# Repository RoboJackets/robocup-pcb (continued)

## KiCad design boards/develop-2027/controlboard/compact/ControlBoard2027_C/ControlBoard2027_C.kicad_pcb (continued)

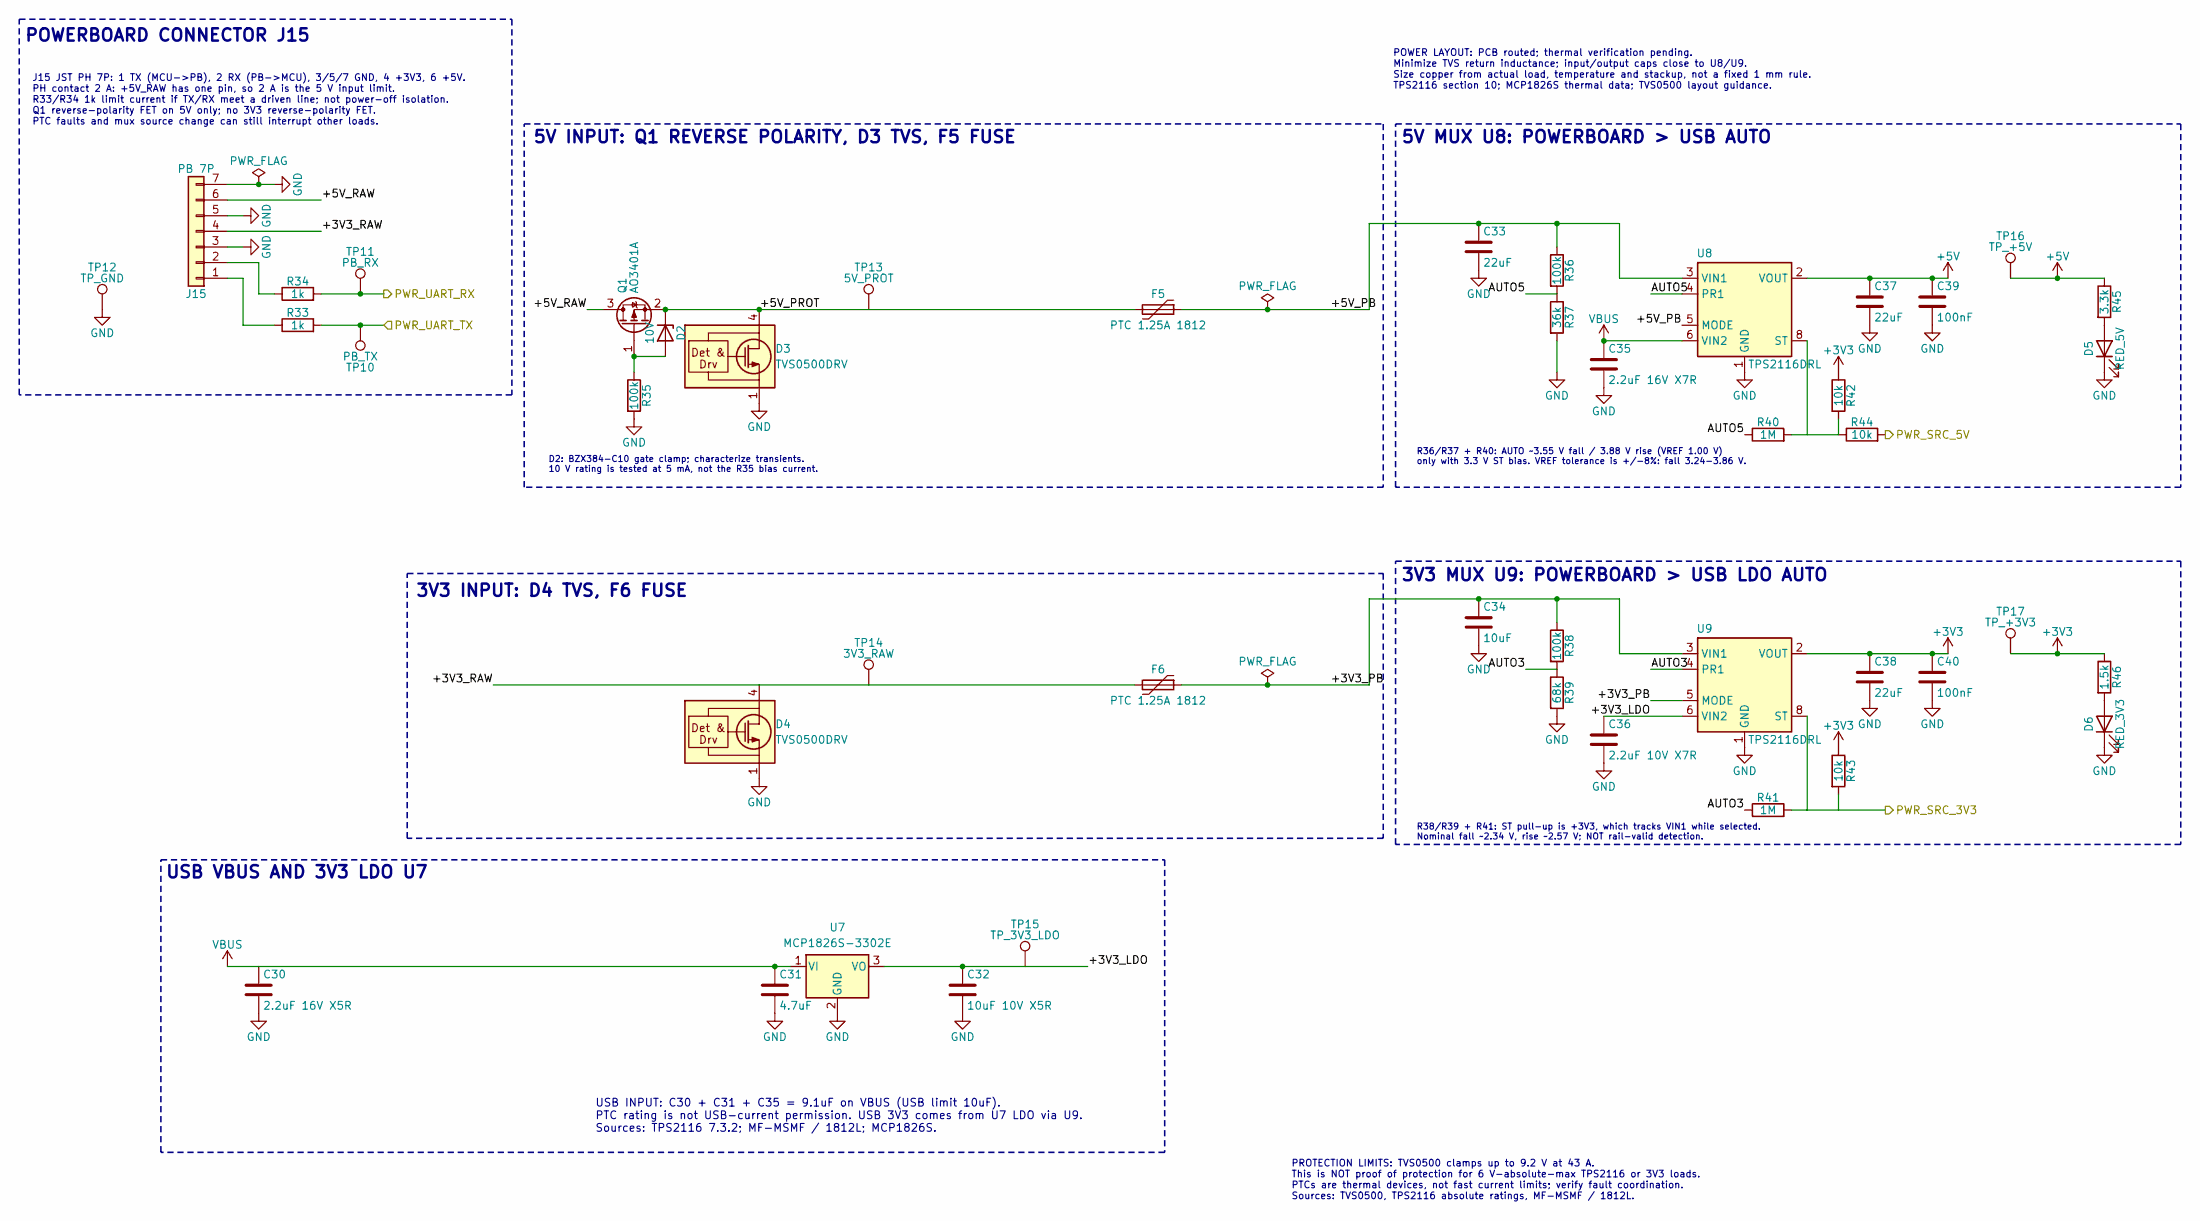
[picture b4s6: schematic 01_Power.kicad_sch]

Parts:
C30: 2.2uF 16V X5R; C_0603_1608Metric; Rating 16V X5R; MPN Samsung CL10A225KO8NNNC; LCSC C23630
C31: 4.7uF; C_0603_1608Metric; Rating 16V X5R; MPN TDK C1608X5R1C475K080AC; LCSC C19666
C32: 10uF 10V X5R; C_0603_1608Metric; Rating 10V X5R 10%; MPN Taiyo Yuden LMK107BBJ106MALT; LCSC C19702
C33, C37: 22uF; C_0805_2012Metric; Rating 25V X5R 20%; MPN Samsung CL21A226MOQNNNE; LCSC C45783
C34: 10uF; C_0603_1608Metric; Rating 10V X5R 10%; MPN Taiyo Yuden LMK107BBJ106MALT; LCSC C19702
C35: 2.2uF 16V X7R; C_0805_2012Metric; Rating 16V X7R; MPN Samsung CL21B225KOFNNNE; LCSC C28234
C36: 2.2uF 10V X7R; C_0603_1608Metric; Rating 10V X7R; MPN Samsung CL10B225KP8NNNC; LCSC C100082
C38: 22uF; C_0603_1608Metric; Rating 6.3V X5R 20%; MPN Taiyo Yuden JMK107BBJ226MA-T; LCSC C59461
C39, C40: 100nF; C_0402_1005Metric; Rating 16V X7R; MPN Samsung CL05B104KO5NNNC; LCSC C1525
D2: 10V; D_SOD-323; MPN Nexperia BZX384-C10,115; LCSC C96228
D3, D4: TVS0500DRV; WSON-6-1EP_2x2mm_P0.65mm_EP1x1.6mm; MPN TI TVS0500DRVR; LCSC C609571
D5: RED_5V; LED_0603_1608Metric; MPN Kingbright APT1608EC; LCSC C5554143
D6: RED_3V3; LED_0603_1608Metric; MPN Kingbright APT1608EC; LCSC C5554143
F5, F6: PTC 1.25A 1812; Fuse_Bourns_MF-MSMF_1812; MPN Bourns MF-MSMF125/16X-2; LCSC C207067
J15: PB 7P; JST_PH_S7B-PH-K_1x07_P2.00mm_Horizontal; MPN JST S7B-PH-K-S(LF)(SN); LCSC C157917
Q1: AO3401A; SOT-23; MPN AOS AO3401A; LCSC C15127
R33, R34: 1k; R_0402_1005Metric; Rating 1%; MPN Yageo RC0402FR-071KL; LCSC C11702
R35, R36, R38: 100k; R_0603_1608Metric; Rating 1%; MPN Yageo RC0603FR-07100KL; LCSC C25803
R37: 36k; R_0603_1608Metric; Rating 1%; MPN Yageo RC0603FR-0736KL; LCSC C114619
R39: 68k; R_0603_1608Metric; Rating 1%; MPN Yageo RC0603FR-0768KL; LCSC C23231
R40, R41: 1M; R_0603_1608Metric; Rating 1%; MPN Yageo RC0603FR-071ML; LCSC C22935
R42, R43, R44: 10k; R_0603_1608Metric; Rating 1%; MPN Panasonic ERJ-3EKF1002V; LCSC C25804
R45: 3.3k; R_0603_1608Metric; Rating 1%; MPN Yageo RC0603FR-073K3L; LCSC C22978
R46: 1.5k; R_0603_1608Metric; Rating 1%; MPN Yageo RC0603FR-071K5L; LCSC C22843
TP10: PB_TX; TestPoint_Pad_1.5x1.5mm
TP11: PB_RX; TestPoint_Pad_1.5x1.5mm
TP12: TP_GND; TestPoint_Pad_1.5x1.5mm
TP13: 5V_PROT; TestPoint_Pad_1.5x1.5mm
TP14: 3V3_RAW; TestPoint_Pad_1.5x1.5mm
TP15: TP_3V3_LDO; TestPoint_Pad_1.5x1.5mm
TP16: TP_+5V; TestPoint_Pad_1.5x1.5mm
TP17: TP_+3V3; TestPoint_Pad_1.5x1.5mm
U7: MCP1826S-3302E; SOT-223-3_TabPin2; Rating 1A, VIN 6.0V max, 3.3V +-2.5%; MPN Microchip MCP1826S-3302E/DB; LCSC C638624
U8, U9: TPS2116DRL; TI_TPS2116_DRL0008A; MPN TI TPS2116DRLR; LCSC C3235557

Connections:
+3V3: C38.1, C40.1, R42.1, R43.1, R46.1, TP17.1 (1_1), U9.2 (VOUT), U9.7 (VOUT); also elsewhere on the board
+5V: C37.1, C39.1, R45.1, TP16.1 (1_1), U8.2 (VOUT), U8.7 (VOUT); also elsewhere on the board
/MCU/PWR_SRC_3V3: R41.2, R43.2, U9.8 (ST); also elsewhere on the board
/MCU/PWR_SRC_5V: R44.2; also elsewhere on the board
/MCU/PWR_UART_RX: R34.2, TP11.1 (1_1); also elsewhere on the board
/MCU/PWR_UART_TX: R33.2, TP10.1 (1_1); also elsewhere on the board
/Power/+3V3_LDO: C32.1, C36.1, TP15.1 (1_1), U7.3 (VO), U9.6 (VIN2)
/Power/+3V3_RAW: D4.4 (IN), D4.5 (IN), D4.6 (IN), F6.2, J15.4, TP14.1 (1_1)
/Power/+5V_PROT: D2.1 (K), D3.4 (IN), D3.5 (IN), D3.6 (IN), F5.2, Q1.2 (S), TP13.1 (1_1)
/Power/+5V_RAW: J15.6, Q1.3 (D)
/Power/AUTO3: R38.2, R39.1, R41.1, U9.4 (PR1)
/Power/AUTO5: R36.2, R37.1, R40.1, U8.4 (PR1)
unnamed: D2.2 (A), Q1.1 (G), R35.1
unnamed: D5.2 (A), R45.2
unnamed: D6.2 (A), R46.2
unnamed: J15.1, R33.1
unnamed: J15.2, R34.1
unnamed: R40.2, R42.2, R44.1, U8.8 (ST)
VBUS: C30.1, C31.1, C35.1, U7.1 (VI), U8.6 (VIN2); also elsewhere on the board

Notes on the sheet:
POWER LAYOUT: PCB routed; thermal verification pending. Minimize TVS return inductance; input/output caps close to U8/U9. Size copper from actual load, temperature and stackup, not a fixed 1 mm rule. TPS2116 section 10; MCP1826S thermal data; TVS0500 layout guidance.
3V3 MUX U9: POWERBOARD > USB LDO AUTO
USB INPUT: C30 + C31 + C35 = 9.1uF on VBUS (USB limit 10uF). PTC rating is not USB-current permission. USB 3V3 comes from U7 LDO via U9. Sources: TPS2116 7.3.2; MF-MSMF / 1812L; MCP1826S.
R36/R37 + R40: AUTO ~3.55 V fall / 3.88 V rise (VREF 1.00 V) only with 3.3 V ST bias. VREF tolerance is +/-8%: fall 3.24-3.86 V.
D2: BZX384-C10 gate clamp; characterize transients. 10 V rating is tested at 5 mA, not the R35 bias current.
J15 JST PH 7P: 1 TX (MCU->PB), 2 RX (PB->MCU), 3/5/7 GND, 4 +3V3, 6 +5V. PH contact 2 A: +5V_RAW has one pin, so 2 A is the 5 V input limit. R33/R34 1k limit current if TX/RX meet a driven line; not power-off isolation. Q1 reverse-polarity FET on 5V only; no 3V3 reverse-polarity FET. PTC faults and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
5V INPUT: Q1 REVERSE POLARITY, D3 TVS, F5 FUSE
5V MUX U8: POWERBOARD > USB AUTO
PROTECTION LIMITS: TVS0500 clamps up to 9.2 V at 43 A. This is NOT proof of protection for 6 V-absolute-max TPS2116 or 3V3 loads. PTCs are thermal devices, not fast current limits; verify fault coordination. Sources: TVS0500, TPS2116 absolute ratings, MF-MSMF / 1812L.
3V3 INPUT: D4 TVS, F6 FUSE
USB VBUS AND 3V3 LDO U7
POWERBOARD CONNECTOR J15
R38/R39 + R41: ST pull-up is +3V3, which tracks VIN1 while selected. Nominal fall ~2.34 V, rise ~2.57 V; NOT rail-valid detection.

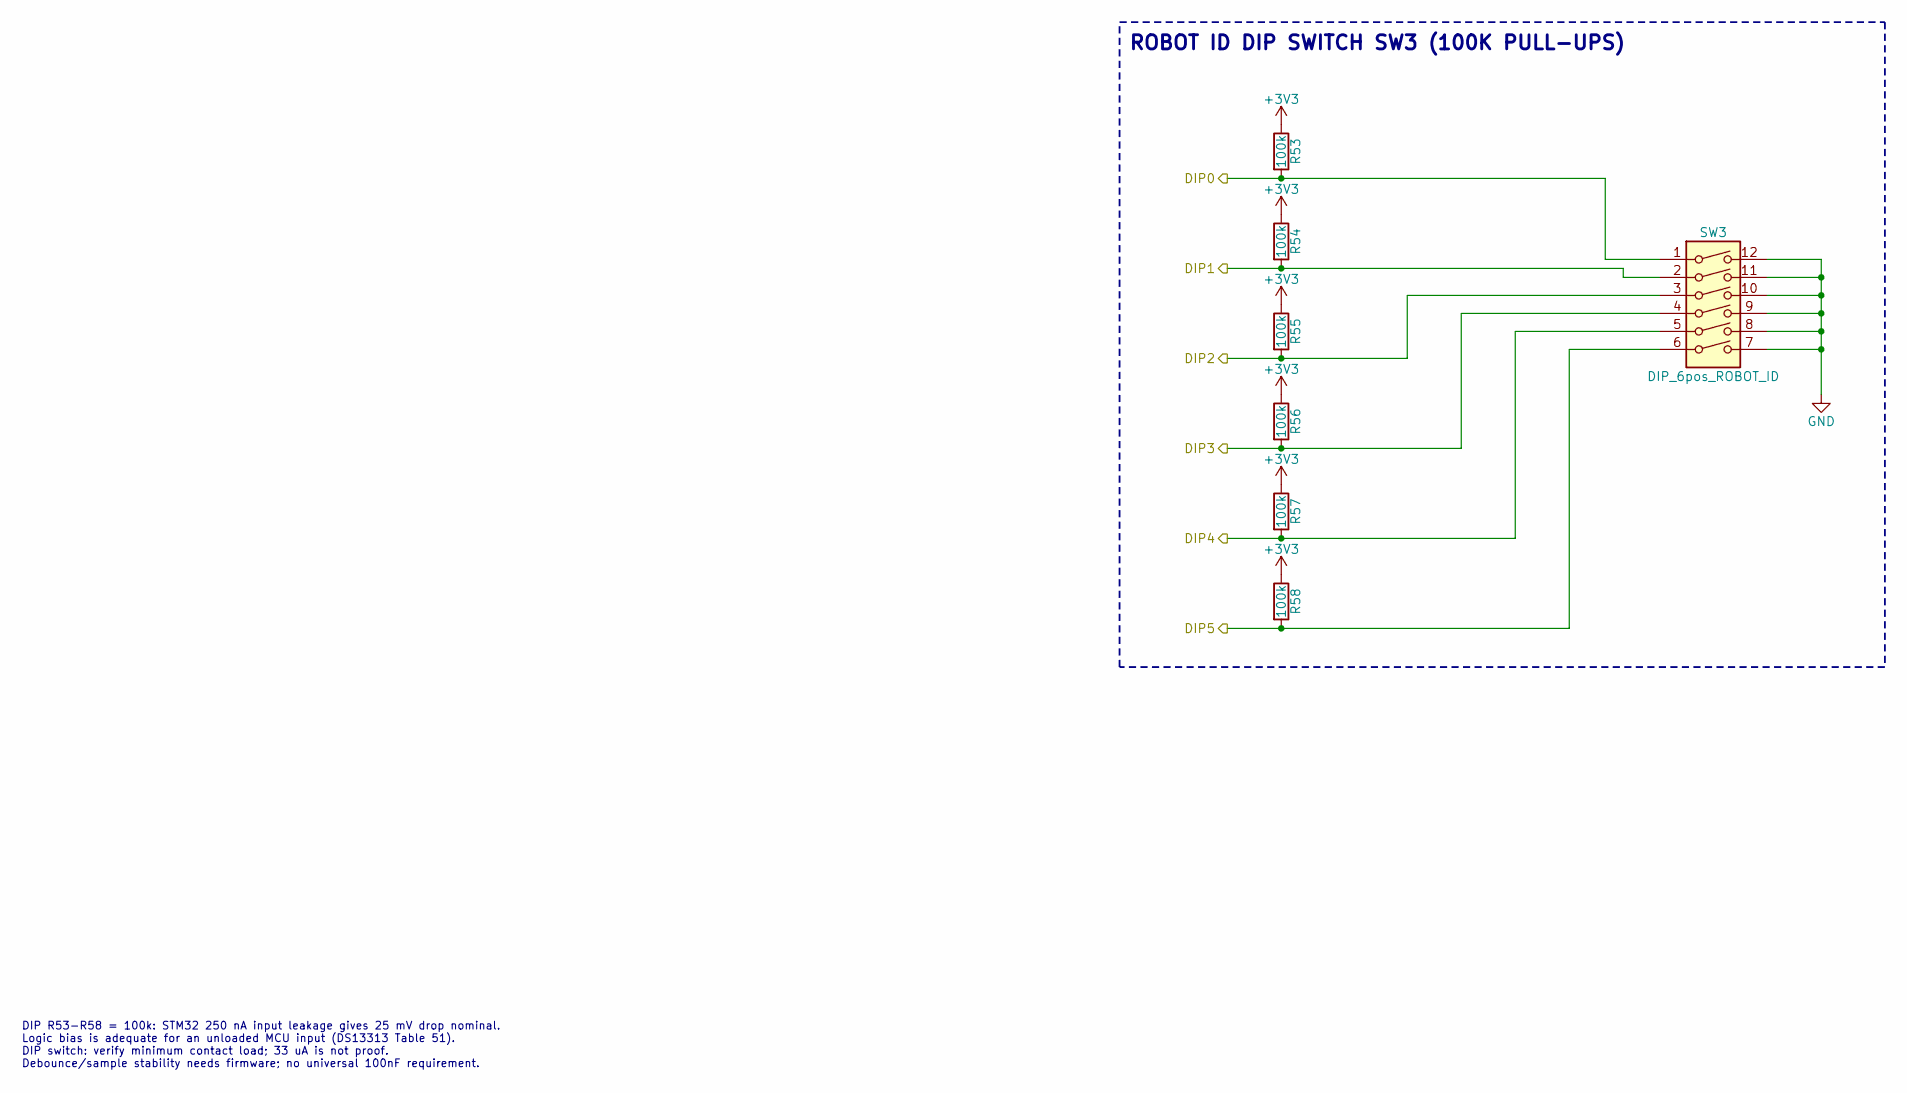
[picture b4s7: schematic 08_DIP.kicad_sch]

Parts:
R53, R54, R55, R56, R57, R58: 100k; R_0603_1608Metric; Rating 1%; MPN Yageo RC0603FR-07100KL; LCSC C25803
SW3: DIP_6pos_ROBOT_ID; SW_DIP_SPSTx06_Slide_6.7x16.8mm_W7.62mm_P2.54mm_LowProfile; MPN CTS 209-6MS; LCSC C129072

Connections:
+3V3: R53.1, R54.1, R55.1, R56.1, R57.1, R58.1; also elsewhere on the board
/MCU/DIP0: R53.2, SW3.1; also elsewhere on the board
/MCU/DIP1: R54.2, SW3.2; also elsewhere on the board
/MCU/DIP2: R55.2, SW3.3; also elsewhere on the board
/MCU/DIP3: R56.2, SW3.4; also elsewhere on the board
/MCU/DIP4: R57.2, SW3.5; also elsewhere on the board
/MCU/DIP5: R58.2, SW3.6; also elsewhere on the board

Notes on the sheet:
DIP R53-R58 = 100k: STM32 250 nA input leakage gives 25 mV drop nominal. Logic bias is adequate for an unloaded MCU input (DS13313 Table 51). DIP switch: verify minimum contact load; 33 uA is not proof. Debounce/sample stability needs firmware; no universal 100nF requirement.
ROBOT ID DIP SWITCH SW3 (100K PULL-UPS)

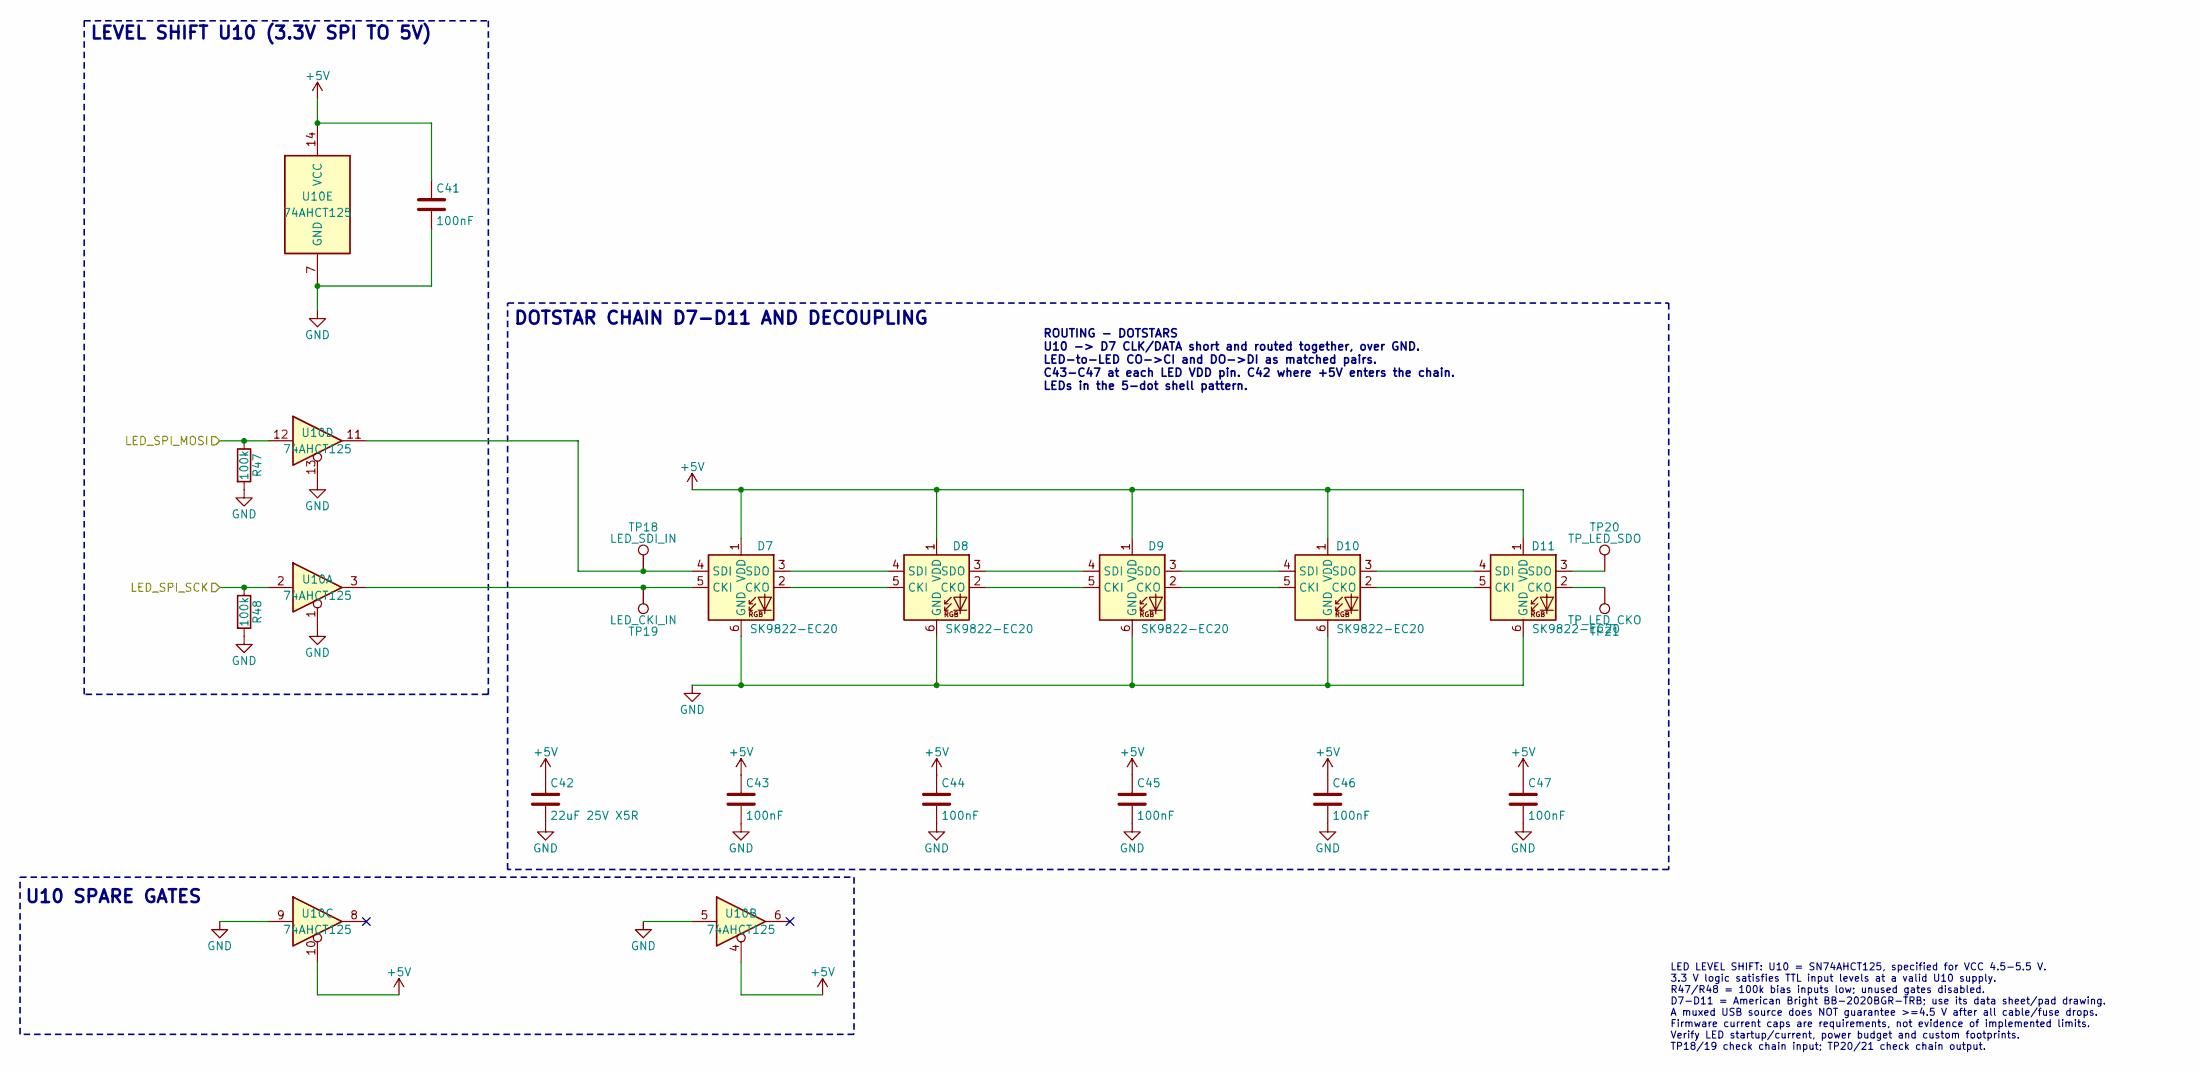
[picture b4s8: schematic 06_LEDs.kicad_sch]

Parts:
C41, C43, C44, C45, C46, C47: 100nF; C_0402_1005Metric; Rating 16V X7R; MPN Samsung CL05B104KO5NNNC; LCSC C1525
C42: 22uF 25V X5R; C_0805_2012Metric; Rating 25V X5R 20%; MPN Samsung CL21A226MOQNNNE; LCSC C45783
D7, D8, D9, D10, D11: SK9822-EC20; OPSCO_SK9822-EC20; MPN OPSCO SK9822-EC20; LCSC C2909059
R47, R48: 100k; R_0402_1005Metric; Rating 1%; MPN Yageo RC0402FR-07100KL; LCSC C25741
TP18: LED_SDI_IN; TestPoint_Pad_1.5x1.5mm
TP19: LED_CKI_IN; TestPoint_Pad_1.5x1.5mm
TP20: TP_LED_SDO; TestPoint_Pad_1.5x1.5mm
TP21: TP_LED_CKO; TestPoint_Pad_1.5x1.5mm
U10: 74AHCT125; SO-14_3.9x8.65mm_P1.27mm; MPN TI SN74AHCT125DR; LCSC C155176

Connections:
+5V: C41.1, C42.1, C43.1, C44.1, C45.1, C46.1, C47.1, D7.1 (VDD), D8.1 (VDD), D9.1 (VDD), D10.1 (VDD), D11.1 (VDD), U10.4, U10.10, U10.14 (VCC); also elsewhere on the board
/DotStar LEDs/LED_SPI_MOSI: R47.1, U10.12; also elsewhere on the board
/DotStar LEDs/LED_SPI_SCK: R48.1, U10.2; also elsewhere on the board
unnamed: D7.5 (CKI), TP19.1 (1_1), U10.3
unnamed: D7.2 (CKO), D8.5 (CKI)
unnamed: D7.4 (SDI), TP18.1 (1_1), U10.11
unnamed: D7.3 (SDO), D8.4 (SDI)
unnamed: D8.2 (CKO), D9.5 (CKI)
unnamed: D8.3 (SDO), D9.4 (SDI)
unnamed: D9.2 (CKO), D10.5 (CKI)
unnamed: D10.2 (CKO), D11.5 (CKI)
unnamed: D9.3 (SDO), D10.4 (SDI)
unnamed: D10.3 (SDO), D11.4 (SDI)
unnamed: D11.2 (CKO), TP21.1 (1_1)
unnamed: D11.3 (SDO), TP20.1 (1_1)

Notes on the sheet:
LED LEVEL SHIFT: U10 = SN74AHCT125, specified for VCC 4.5-5.5 V. 3.3 V logic satisfies TTL input levels at a valid U10 supply. R47/R48 = 100k bias inputs low; unused gates disabled. D7-D11 = American Bright BB-2020BGR-TRB; use its data sheet/pad drawing. A muxed USB source does NOT guarantee >=4.5 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
LEVEL SHIFT U10 (3.3V SPI TO 5V)
U10 SPARE GATES
DOTSTAR CHAIN D7-D11 AND DECOUPLING
ROUTING - DOTSTARS U10 -> D7 CLK/DATA short and routed together, over GND. LED-to-LED CO->CI and DO->DI as matched pairs. C43-C47 at each LED VDD pin. C42 where +5V enters the chain. LEDs in the 5-dot shell pattern.

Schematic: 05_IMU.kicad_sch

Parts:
C48, C49: 100nF; C_0402_1005Metric; Rating 16V X7R; MPN Samsung CL05B104KO5NNNC; LCSC C1525
U11: LSM6DSV320X; ST_LGA-14L_2.5x3mm_P0.5mm; MPN ST LSM6DSV320XTR

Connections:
+3V3: C48.1, C49.1, U11.5 (VDDIO), U11.8 (VDD), U11.12 (CS); also elsewhere on the board
/IMU/ACCEL_EXTI: U11.4 (INT1); also elsewhere on the board
/IMU/GYRO_EXTI: U11.9 (INT2); also elsewhere on the board
/IMU/IMU_I2C_SCL: U11.13 (SCL); also elsewhere on the board
/IMU/IMU_I2C_SDA: U11.14 (SDA); also elsewhere on the board

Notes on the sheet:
ROUTING - IMU C48 (VDDIO pin 5), C49 (VDD pin 8): 100nF, as close to the pins as possible. CS to VDDIO = I2C. TA0, SDx, SCx to GND: address 0x6A, mode 1 (DS14623 Fig. 27). OCS_aux/SDO_aux open. No traces or vias under the package.
IMU U11 LSM6DSV320X: I2C (0x6A), INT1/INT2 INTERRUPTS
INTERRUPTS: INT1 -> ACCEL_EXTI (PF3), INT2 -> GYRO_EXTI (PF2). Both are push-pull and are driven low from power-up (DS14623 Table 25), so no pull-downs are fitted. Route data-ready or events to them with INT1_CTRL/INT2_CTRL.

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
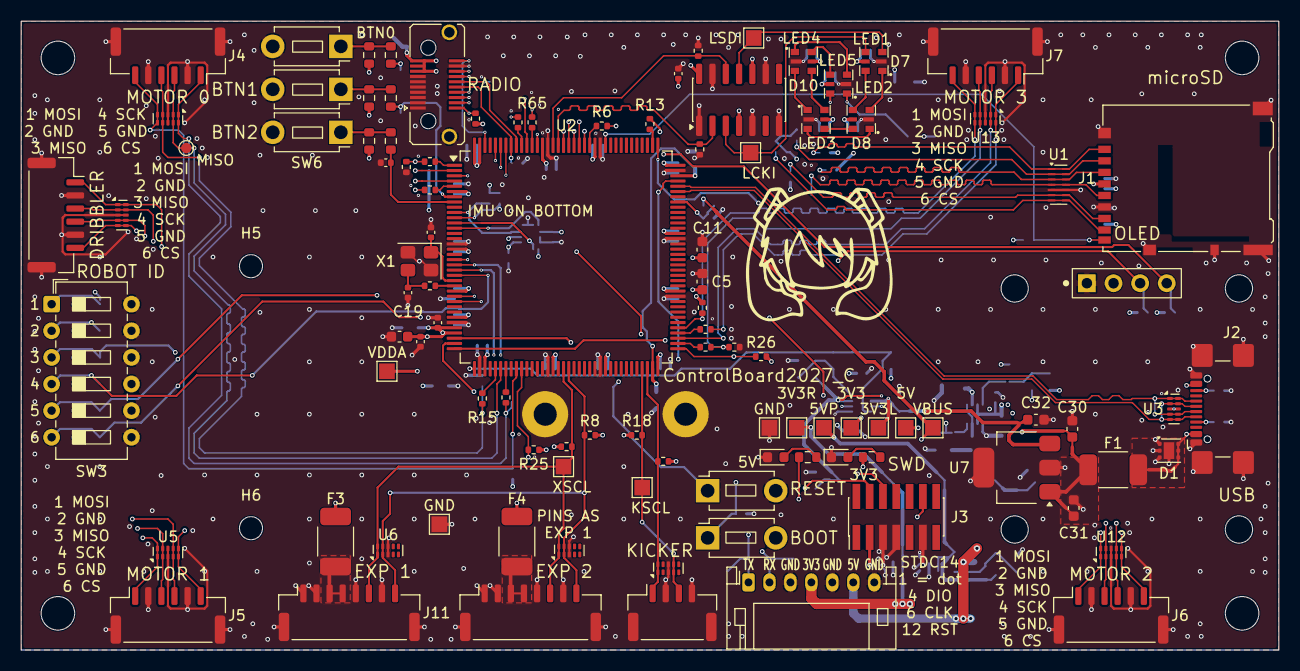
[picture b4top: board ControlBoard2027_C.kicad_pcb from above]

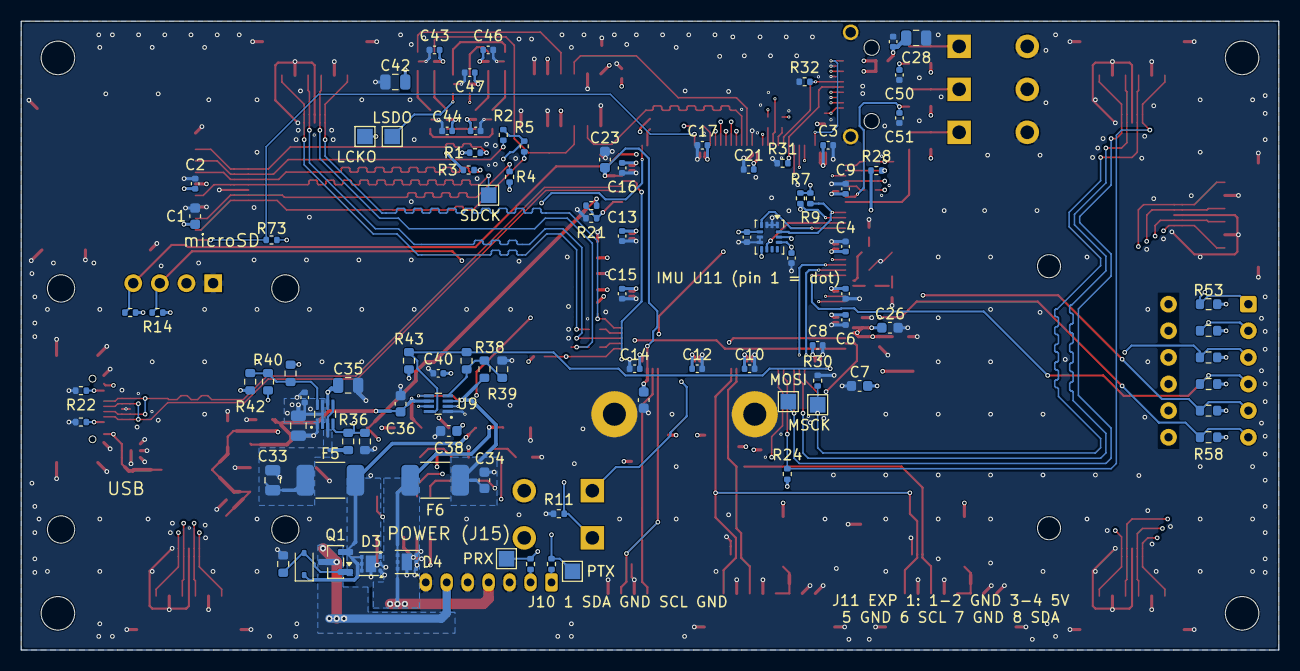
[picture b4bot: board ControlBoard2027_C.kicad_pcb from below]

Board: 6 copper layers, 120.0 x 60.0 mm, 204 parts (94 on the bottom side), 112 nets.

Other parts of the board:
HR1, HR2: Radio standoff M2; MountingHole_2.2mm_M2_Pad

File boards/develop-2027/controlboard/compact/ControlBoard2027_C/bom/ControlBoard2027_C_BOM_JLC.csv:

Comment,Designator,Footprint,LCSC Part #
10uF / 10uF 10V X5R,"C1,C5,C32,C34",C_0603_1608Metric,C19702
100nF,"C2,C3,C4,C6,C8,C9,C10,C12,C13,C14,C15,C16,C17,C20,C21,C25,C27,C29,C39,C40,C41,C43,C44,C45,C46,C47,C48,C49,C50,C51,C52",C_0402_1005Metric,C1525
4.7uF 16V X5R / 4.7uF,"C7,C11,C31",C_0603_1608Metric,C19666
12pF,"C18,C19",C_0402_1005Metric,C1547
2.2uF / 2.2uF 10V X7R,"C22,C23,C36",C_0603_1608Metric,C100082
1uF 50V X5R,"C24,C26",C_0603_1608Metric,C15849
22uF / 22uF 25V X5R,"C28,C33,C37,C42",C_0805_2012Metric,C45783
2.2uF 16V X5R,C30,C_0603_1608Metric,C23630
2.2uF 16V X7R,C35,C_0805_2012Metric,C28234
22uF,C38,C_0603_1608Metric,C59461
TVS0500DRV,"D1,D3,D4",WSON-6-1EP_2x2mm_P0.65mm_EP1x1.6mm,C609571
10V,D2,D_SOD-323,C96228
RED_5V / RED_3V3,"D5,D6",LED_0603_1608Metric,C5554143
SK9822-EC20,"D7,D8,D9,D10,D11",OPSCO_SK9822-EC20,C2909059
PTC 0.75A 1812,"F1,F3,F4",Fuse_Bourns_MF-MSMF_1812,C207065
PTC 1.25A 1812,"F5,F6",Fuse_Bourns_MF-MSMF_1812,C207067
microSD_SDIO,J1,microSD_HC_Hirose_DM3AT-SF-PEJM5,C114218
USB-C_DFU,J2,USB_C_Receptacle_GCT_USB4110,C5143397
STDC14,J3,PinHeader_2x07_P1.27mm_Vertical_SMD,C5307809
MOTOR0 / MOTOR1 / MOTOR2 / MOTOR3 / DRIBBLER,"J4,J5,J6,J7,J8",JST_GH_SM06B-GHS-TB_1x06-1MP_P1.25mm_Horizontal,C133065
RADIO_MEZZ,J9,Samtec_LSHM-110-xx.x-x-DV-S_2x10-1SH_P0.50mm_Vertical_PIH,C3643542
KICKER_I2C,J10,JST_GH_SM04B-GHS-TB_1x04-1MP_P1.25mm_Horizontal,C189895
EXP_1 / EXP_2,"J11,J12",JST_GH_SM08B-GHS-TB_1x08-1MP_P1.25mm_Horizontal,C265111
OLED,J13,OLED_0.96in_SSD1306_I2C_Module_Socket_1x04_P2.54mm,C2718488
PB 7P,J15,JST_PH_S7B-PH-K_1x07_P2.00mm_Horizontal,C157917
AO3401A,Q1,SOT-23,C15127
47k,"R1,R2,R3,R4,R5,R20,R73",R_0402_1005Metric,C25792
30R,"R6,R15,R16,R65,R66,R67,R68,R70,R71",R_0402_1005Metric,C2479340
2.2k,"R7,R8,R9,R10,R14,R17,R18,R19",R_0402_1005Metric,C25879
10k,"R11,R13,R24,R25,R26,R27,R28,R29,R32",R_0402_1005Metric,C25744
0R,R12,R_0402_1005Metric,C17168
68k,R21,R_0402_1005Metric,C482226
5.1k,"R22,R23",R_0402_1005Metric,C25905
100k,"R30,R31,R47,R48,R69,R72",R_0402_1005Metric,C25741
1k,"R33,R34",R_0402_1005Metric,C11702
100k,"R35,R36,R38,R53,R54,R55,R56,R57,R58",R_0603_1608Metric,C25803
36k,R37,R_0603_1608Metric,C114619
68k,R39,R_0603_1608Metric,C23231
1M,"R40,R41",R_0603_1608Metric,C22935
10k,"R42,R43,R44,R59,R60,R61,R62,R63,R64",R_0603_1608Metric,C25804
3.3k,R45,R_0603_1608Metric,C22978
1.5k,R46,R_0603_1608Metric,C22843
RESET / BOOT0_DFU / USER_BTN0 / USER_BTN1 / USER_BTN2,"SW1,SW2,SW4,SW5,SW6",SW_PUSH_1P1T_6x3.5mm_H4.3_APEM_MJTP1243,C2689636
DIP_6pos_ROBOT_ID,SW3,SW_DIP_SPSTx06_Slide_6.7x16.8mm_W7.62mm_P2.54mm_LowProfile,C129072
TPD6E05U06RVZ,U1,Texas_R-PUSON-N14,C962978
STM32H723ZGT6,U2,LQFP-144_20x20mm_P0.5mm,C730146
TPD4E05U06DQA,"U3,U4,U5,U6,U12,U13,U14,U16,U17",USON-10_2.5x1.0mm_P0.5mm,C138714
MCP1826S-3302E,U7,SOT-223-3_TabPin2,C638624
TPS2116DRL,"U8,U9",TI_TPS2116_DRL0008A,C3235557
74AHCT125,U10,SO-14_3.9x8.65mm_P1.27mm,C155176
25MHz 10pF,X1,Crystal_SMD_3225-4Pin_3.2x2.5mm,C5366868

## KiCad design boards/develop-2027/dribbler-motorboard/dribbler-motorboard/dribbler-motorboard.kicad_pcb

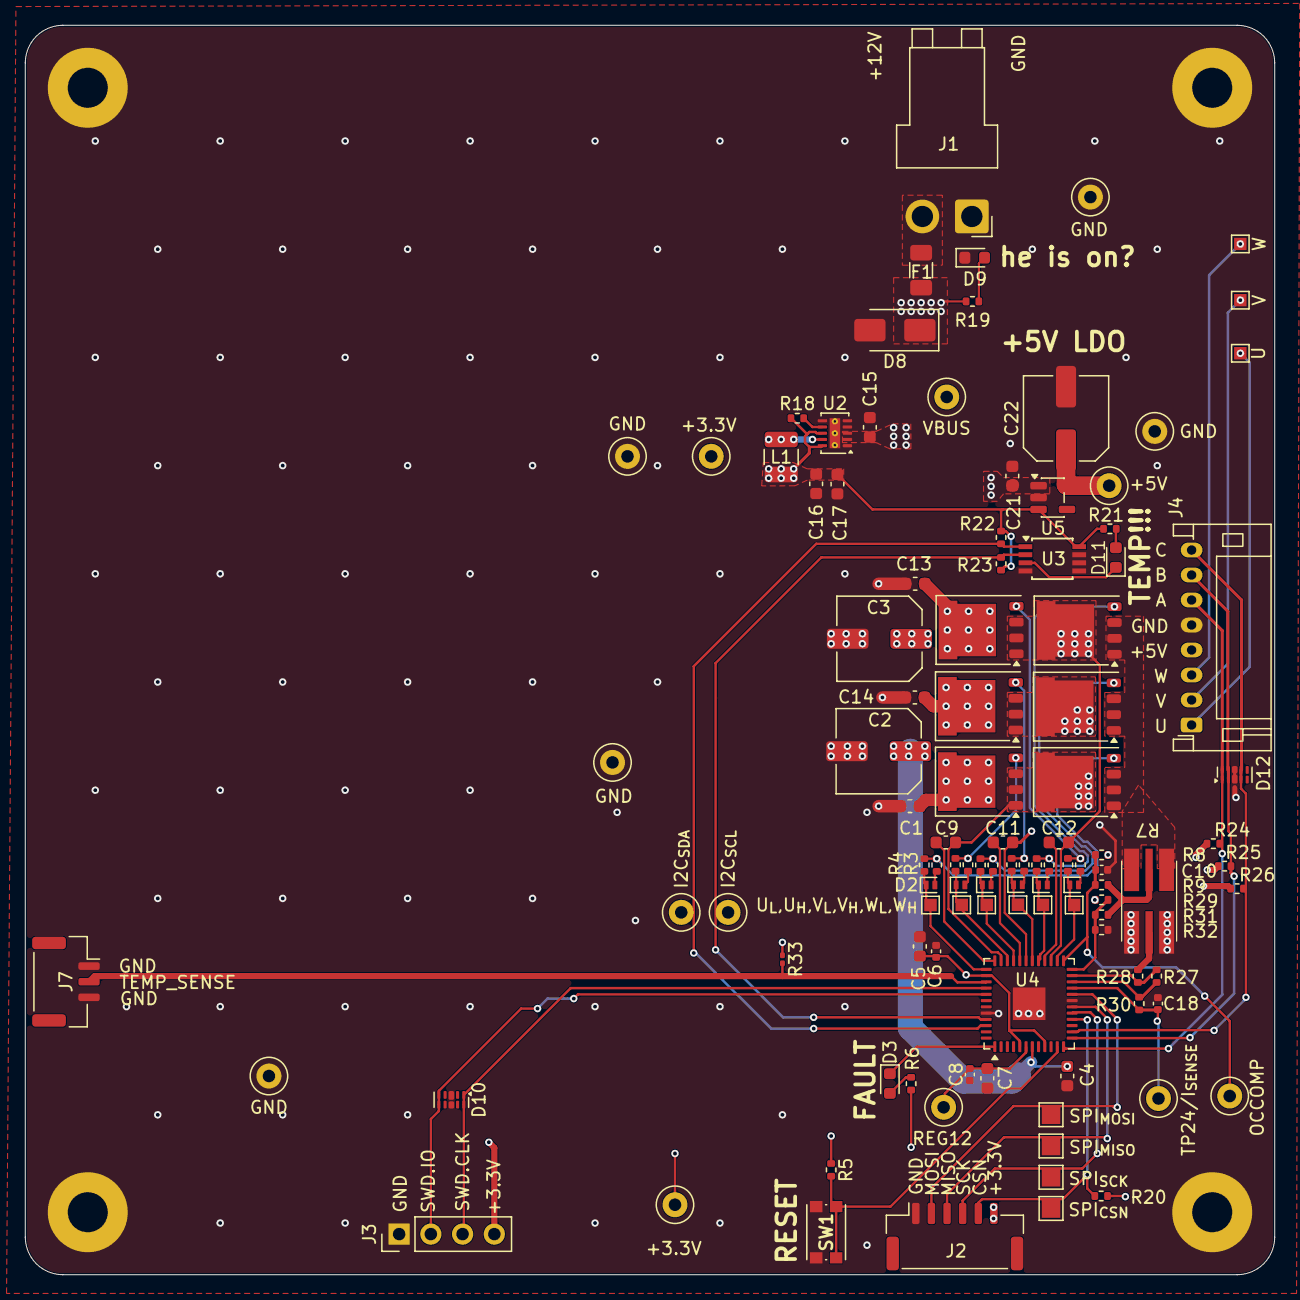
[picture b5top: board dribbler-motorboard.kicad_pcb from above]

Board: 4 copper layers, 100.0 x 100.0 mm, 114 parts (0 on the bottom side), 58 nets.

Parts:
+3.3V: 3.3V REG; TestPoint_Loop_D1.80mm_Drill1.0mm_Beaded
+3.3V#2: +5V EXT; TestPoint_Loop_D1.80mm_Drill1.0mm_Beaded
+5V: +5V; TestPoint_Loop_D1.80mm_Drill1.0mm_Beaded
C1, C4, C5, C9, C11, C12, C13, C14, C15, C21: 1u 63V; C_0603_1608Metric
C2, C3, C22: 100u 35V; C_Elec_6.3x5.8
C6, C8, C18: 100n 25V; C_0402_1005Metric
C7, C16, C17: 10u 25V; C_0603_1608Metric
C10: 33nF; C_0402_1005Metric
D1, D2, D4, D5, D6, D7: 1N4148WL2-TP; D_SOD-882
D3: FAULT; LED_0603_1608Metric
D8: SMAJ16A; D_SMA
D9: +12V; LED_0603_1608Metric
D10, D12: PUSB3FR4Z; Diodes_UDFN-10_1x2.5mm_P0.5mm
D11: OVERTEMP; LED_0603_1608Metric
F1: 12A; Fuse_1206_3216Metric
GND: GND; TestPoint_Loop_D1.80mm_Drill1.0mm_Beaded
GND#2, GND#4, GND#5: GND; TestPoint_Loop_D1.80mm_Drill1.0mm_Beaded
GND#3: GND EXT; TestPoint_Loop_D1.80mm_Drill1.0mm_Beaded
H1, H2, H3, H4: Corner; MountingHole_3.2mm_M3_Pad
I2C_{SCL}: SCL; TestPoint_Loop_D1.80mm_Drill1.0mm_Beaded
I2C_{SDA}: SDA; TestPoint_Loop_D1.80mm_Drill1.0mm_Beaded
J1: PWR_IN; JST_VH_B2PS-VH_1x02_P3.96mm_Horizontal
J2: COMM SPI; JST_GH_SM06B-GHS-TB_1x06-1MP_P1.25mm_Horizontal
J3: SWD Debug; PinHeader_1x04_P2.54mm_Vertical
J4: MOTOR PHASE; JST_PH_S8B-PH-K_1x08_P2.00mm_Horizontal
J7: Conn_01x03; JST_GH_SM03B-GHS-TB_1x03-1MP_P1.25mm_Horizontal
L1: 10u 540mA; L_1210_3225Metric
OCCOMP: OCCOMP; TestPoint_Loop_D1.80mm_Drill1.0mm_Beaded
Q1, Q2, Q3, Q4, Q5, Q6: STL90N10F7; PQFN-8-EP_6x5mm_P1.27mm_Generic
R1, R3, R10, R12, R14, R16: 0R; R_0402_1005Metric
R2, R4, R11, R13, R15, R17: 68R; R_0402_1005Metric
R5, R19, R20, R24, R25, R26: 10k; R_0402_1005Metric
R6, R21, R22, R23: 4.7k; R_0402_1005Metric
R7: 15m ±1% 3W; R_Shunt_Analog_2512_6332_HighAccuracy
R8: 1.13k ±0.1%; R_0402_1005Metric
R9: 33 ±0.1%; R_0402_1005Metric
R18: 100k; R_0402_1005Metric
R27: 120k ±0.1%; R_0402_1005Metric
R28, R31: 30k ±0.1%; R_0402_1005Metric
R29, R32: 240k ±0.1%; R_0402_1005Metric
R30: 300R ±1%; R_0402_1005Metric
R33: 10k; R_0201_0603Metric
REG12: REG12; TestPoint_Loop_D1.80mm_Drill1.0mm_Beaded
SPI_{CSN}: CSN; TestPoint_Pad_1.5x1.5mm
SPI_{MISO}: MISO; TestPoint_Pad_1.5x1.5mm
SPI_{MOSI}: MOSI; TestPoint_Pad_1.5x1.5mm
SPI_{SCK}: SCK; TestPoint_Pad_1.5x1.5mm
SW1: RESET; SW_Push_1P1T_NO_CK_KMR2
TP4: HSU; TestPoint_Pad_1.0x1.0mm
TP6: HSV; TestPoint_Pad_1.0x1.0mm
TP7: LSV; TestPoint_Pad_1.0x1.0mm
TP8: HSW; TestPoint_Pad_1.0x1.0mm
TP9: LSW; TestPoint_Pad_1.0x1.0mm
TP24/I_{SENSE}: ISENSEx; TestPoint_Loop_D1.80mm_Drill1.0mm_Beaded
U: OUT_{x}; TestPoint_Pad_1.0x1.0mm
U2: TPS62177DQC; WSON-10-1EP_2x3mm_P0.5mm_EP0.84x2.4mm_ThermalVias
U3: LM75ADP; TSSOP-8_3x3mm_P0.65mm
U4: STSPIN32G0B2; VQFN-48-1EP_7x7mm_P0.5mm_EP2.6x2.6mm
U5: LDI559-05EN; SOT-23-5
U_{L},U_{H},V_{L},V_{H},W_{L},W_{H}: LSU; TestPoint_Pad_1.0x1.0mm
V: OUT_{x}; TestPoint_Pad_1.0x1.0mm
VBUS: VBUS; TestPoint_Loop_D1.80mm_Drill1.0mm_Beaded
W: OUT_{x}; TestPoint_Pad_1.0x1.0mm

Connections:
+3.3V: +3.3V.1 (1_1), +3.3V#2.1 (1_1), C5.1, C6.1, C16.1, C17.1, J2.6, J3.4, L1.2, R5.1, R6.1, R8.2, R18.1, R20.1, R21.1, R22.1, R23.1, R24.1, R25.1, R26.1, R29.1, R33.1, U2.8 (~SLEEP), U2.10 (VOS), U3.8 (VCC), U4.5 (VDD), U4.9 (REG3V3), U4.38 (~STBY), U5.3 (EN)
+5V: +5V.1 (1_1), C22.1, J4.4 (+5V), U5.5 (VOUT)
/External Connections/SPI.CSN: J2.5, R20.2, SPI_{CSN}.1 (1_1), U4.16 (PA4/SPI1_~SS)
/External Connections/SPI.MISO: J2.3, SPI_{MISO}.1 (1_1), U4.18 (PA6/SPI1_MISO)
/External Connections/SPI.MOSI: J2.2, SPI_{MOSI}.1 (1_1), U4.20 (PA7/SPI1_MOSI)
/External Connections/SPI.SCK: J2.4, SPI_{SCK}.1 (1_1), U4.17 (PA5/SPI1_SCK)
/MOSFET Temperature Sensor/I2C.SCL: I2C_{SCL}.1 (1_1), R23.2, U3.2 (SCL), U4.45 (PB6/I2C1_SCL)
/MOSFET Temperature Sensor/I2C.SDA: I2C_{SDA}.1 (1_1), R22.2, U3.1 (SDA), U4.46 (PB7/I2C1_SDA)
/Motor Connections/HALL.A: D12.1 (CH1), D12.10 (CH1), J4.6 (HALL_A), R24.2, U4.12 (PA0/TIM2_CH1)
/Motor Connections/HALL.B: D12.2 (CH2), D12.9 (CH2), J4.7 (HALL_B), R25.2, U4.13 (PA1/TIM2_CH2)
/Motor Connections/HALL.C: D12.4 (CH3), D12.7 (CH3), J4.8 (HALL_C), R26.2, U4.14 (PA2/TIM2_CH3)
/Motor Connections/MOTORU: C9.2, J4.1 (PHASE_U), Q1.1 (S), Q1.2 (S), Q1.3 (S), Q2.5 (D), U.1 (1_1), U4.35 (OUTU)
/Motor Connections/MOTORV: C11.2, J4.2 (PHASE_V), Q3.1 (S), Q3.2 (S), Q3.3 (S), Q4.5 (D), U4.31 (OUTV), V.1 (1_1)
/Motor Connections/MOTORW: C12.2, J4.3 (PHASE_W), Q5.1 (S), Q5.2 (S), Q5.3 (S), Q6.5 (D), U4.27 (OUTW), W.1 (1_1)
/Motor Controller/Current Sensing/OPxN: R27.1, R28.2, U4.23 (OP1N)
/Motor Controller/Current Sensing/OPxO: R27.2, R30.1, U4.22 (OP1O)
/Motor Controller/Current Sensing/OPxP: R29.2, R31.2, R32.1, U4.24 (OP1P)
/Motor Controller/FAULT: D3.1 (K), U4.1 (PC13)
/Motor Controller/I_{SENSE}: C18.1, R30.2, TP24/I_{SENSE}.1 (1_1), U4.21 (PB1/ADC_IN)
/Motor Controller/Motor Phase U/HSx: D1.1 (K), R2.1, TP4.1 (1_1), U4.34 (HSU)
/Motor Controller/Motor Phase U/LSx: D2.1 (K), R4.1, U4.37 (LSU), U_{L},U_{H},V_{L},V_{H},W_{L},W_{H}.1 (1_1)
/Motor Controller/Motor Phase V/HSx: D4.1 (K), R11.1, TP6.1 (1_1), U4.30 (HSV)
/Motor Controller/Motor Phase V/LSx: D5.1 (K), R13.1, TP7.1 (1_1), U4.33 (LSV)
/Motor Controller/Motor Phase W/HSx: D6.1 (K), R15.1, TP8.1 (1_1), U4.26 (HSW)
/Motor Controller/Motor Phase W/LSx: D7.1 (K), R17.1, TP9.1 (1_1), U4.29 (LSW)
/Motor Controller/SHUNTN: R7.3, R28.1
/Motor Controller/SHUNTP: R7.2, R9.1, R31.1
/Motor Controller/SHUNT_H: Q2.1 (S), Q2.2 (S), Q2.3 (S), Q4.1 (S), Q4.2 (S), Q4.3 (S), Q6.1 (S), Q6.2 (S), Q6.3 (S), R7.1
/Motor Controller/SWD.CLK: D10.1 (CH1), D10.10 (CH1), J3.3, U4.40 (PA13/SWCLK)
/Motor Controller/SWD.IO: D10.5 (CH5), D10.6 (CH5), J3.2, U4.41 (PA14/SWDIO/BOOT0)
/Motor Controller/TEMP_SENSE: J7.2, R33.2, U4.39 (PA12[PA10]/SPI2_MOSI)
/Motor Controller/~RST: R5.2, SW1.2 (B), U4.11 (PF2/~RST)
GND: C1.2, C2.2, C3.2, C4.2, C5.2, C6.2, C7.2, C8.2, C10.2, C13.2, C14.2, C15.2, C16.2, C17.2, C18.2, C21.1, C22.2, D8.2 (A2), D9.1 (K), D10.3 (GND), D10.8 (GND), D12.3 (GND), D12.8 (GND), GND.1 (1_1), GND#2.1 (1_1), GND#3.1 (1_1), GND#4.1 (1_1), GND#5.1 (1_1), H1.1 (1_1), H2.1 (1_1), H3.1 (1_1), H4.1 (1_1), J1.1, J2.1, J3.1, J4.5 (GND), J7.1, J7.3, R7.4, R32.2, SW1.1 (A), U2.1 (PGND), U2.4 (NC), U2.5 (FB), U2.6 (AGND), U2.11 (PAD), U3.4 (GND), U3.5 (A2), U3.6 (A1), U3.7 (A0), U4.19 (TESTMODE), U4.44 (GND), U4.49 (EPAD), U5.2 (GND)
unnamed: D1.2 (A), R1.1
unnamed: D2.2 (A), R3.1
unnamed: D3.2 (A), R6.2
unnamed: D4.2 (A), R10.1
unnamed: D5.2 (A), R12.1
unnamed: D6.2 (A), R14.1
unnamed: D7.2 (A), R16.1
unnamed: D9.2 (A), R19.2
unnamed: D11.2 (A), R21.2
unnamed: D11.1 (K), U3.3 (OS)
unnamed: F1.1, J1.2
unnamed: Q1.4 (G), R1.2, R2.2
unnamed: Q2.4 (G), R3.2, R4.2
unnamed: Q3.4 (G), R10.2, R11.2
unnamed: Q4.4 (G), R12.2, R13.2
unnamed: Q5.4 (G), R14.2, R15.2
unnamed: Q6.4 (G), R16.2, R17.2
unnamed: R18.2, U2.7 (PG)
unnamed: L1.1, U2.9 (SW)
unnamed: C7.1, C8.1, REG12.1 (1_1), U4.6 (REG12)
unnamed: C9.1, U4.36 (VBOOTU)
unnamed: C11.1, U4.32 (VBOOTV)
unnamed: C12.1, U4.28 (VBOOTW)
unnamed: C10.1, OCCOMP.1 (1_1), R8.1, R9.2, U4.25 (OCCOMP)
VBUS: C1.1, C2.1, C3.1, C4.1, C13.1, C14.1, C15.1, C21.2, D8.1 (A1), F1.2, Q1.5 (D), Q3.5 (D), Q5.5 (D), R19.1, U2.2 (VIN), U2.3 (EN), U4.7 (VM), U5.1 (VIN), VBUS.1 (1_1)

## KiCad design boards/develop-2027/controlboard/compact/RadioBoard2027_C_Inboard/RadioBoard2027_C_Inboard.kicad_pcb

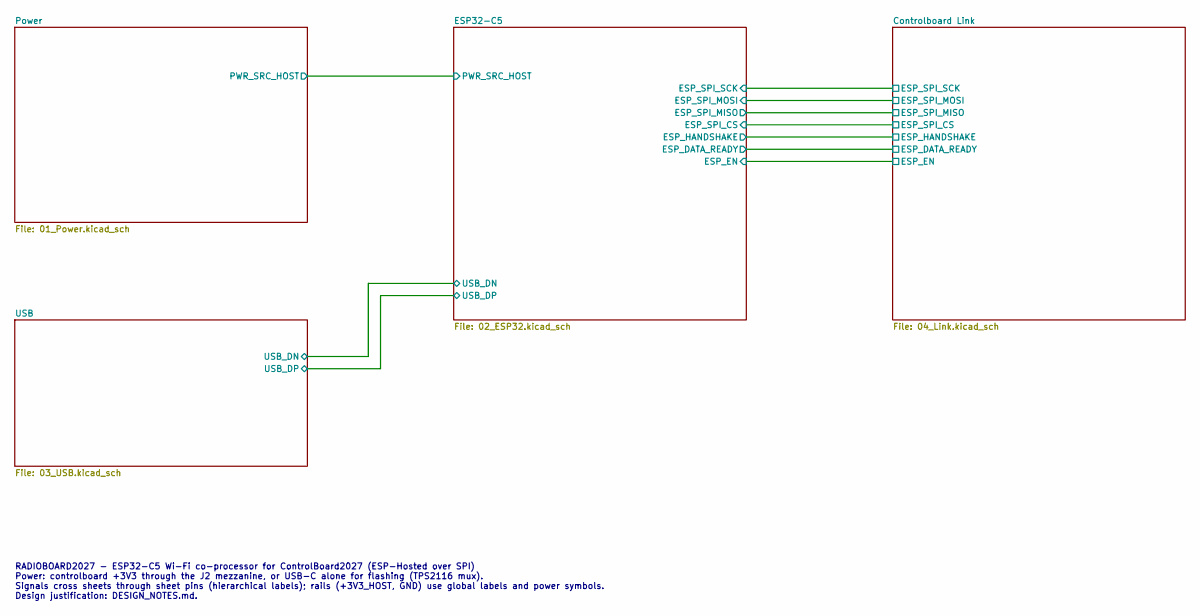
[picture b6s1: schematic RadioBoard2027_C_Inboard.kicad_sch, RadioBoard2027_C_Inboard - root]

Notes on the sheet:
RADIOBOARD2027 - ESP32-C5 Wi-Fi co-processor for ControlBoard2027 (ESP-Hosted over SPI) Power: controlboard +3V3 through the J2 mezzanine, or USB-C alone for flashing (TPS2116 mux). Signals cross sheets through sheet pins (hierarchical labels); rails (+3V3_HOST, GND) use global labels and power sym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
